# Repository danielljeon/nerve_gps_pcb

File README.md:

# nerve_gps_pcb

GPS module to [`nerve_pcb`](https://github.com/danielljeon/nerve_pcb).

---

<details markdown="1">
  <summary>Table of Contents</summary>

<!-- TOC -->
* [nerve_gps_pcb](#nerve_gps_pcb)
  * [1 Overview](#1-overview)
  * [2 Board Specifications](#2-board-specifications)
    * [2.1 Connectors](#21-connectors)
  * [3 Release Notes](#3-release-notes)
    * [3.1 v0.1.0-alpha](#31-v010-alpha)
    * [3.2 v0.1.0](#32-v010)
<!-- TOC -->

</details>

---

## 1 Overview

|                         Top                          |                           Bottom                           |                     v0.1.0-alpha                     |
|:----------------------------------------------------:|:----------------------------------------------------------:|:----------------------------------------------------:|
|  |  |  |

---

## 2 Board Specifications

### 2.1 Connectors

Connectors fixed by hardware (PCB traces or the connector itself).

| Connector                      | Ref | Description                                       |
|--------------------------------|:---:|---------------------------------------------------|
| Bottom side 2x8 board-to-board | J1  | See schematic/layout for details                  |
| WS2812B PWM breakout           | J2  | Pin 1: PWM RGB, Pin 2: Ground                     |
| 5 V GPIO breakout              | J3  | Pin 1: 5 V, Pin 2-4: GPIO1-3 (5 V), Pin 5: Ground |

---

## 3 Release Notes

### 3.1 v0.1.0-alpha

- Pre-release 4-layer board variant.
    - Short-term pre-release board bring-up/testing release.
- Order date: 2025/01/13.

### 3.2 v0.1.0

- Minor changes from the previous `v0.1.0-alpha` pre-release version.
    - Fixed the Double-inverted UART connection issue.

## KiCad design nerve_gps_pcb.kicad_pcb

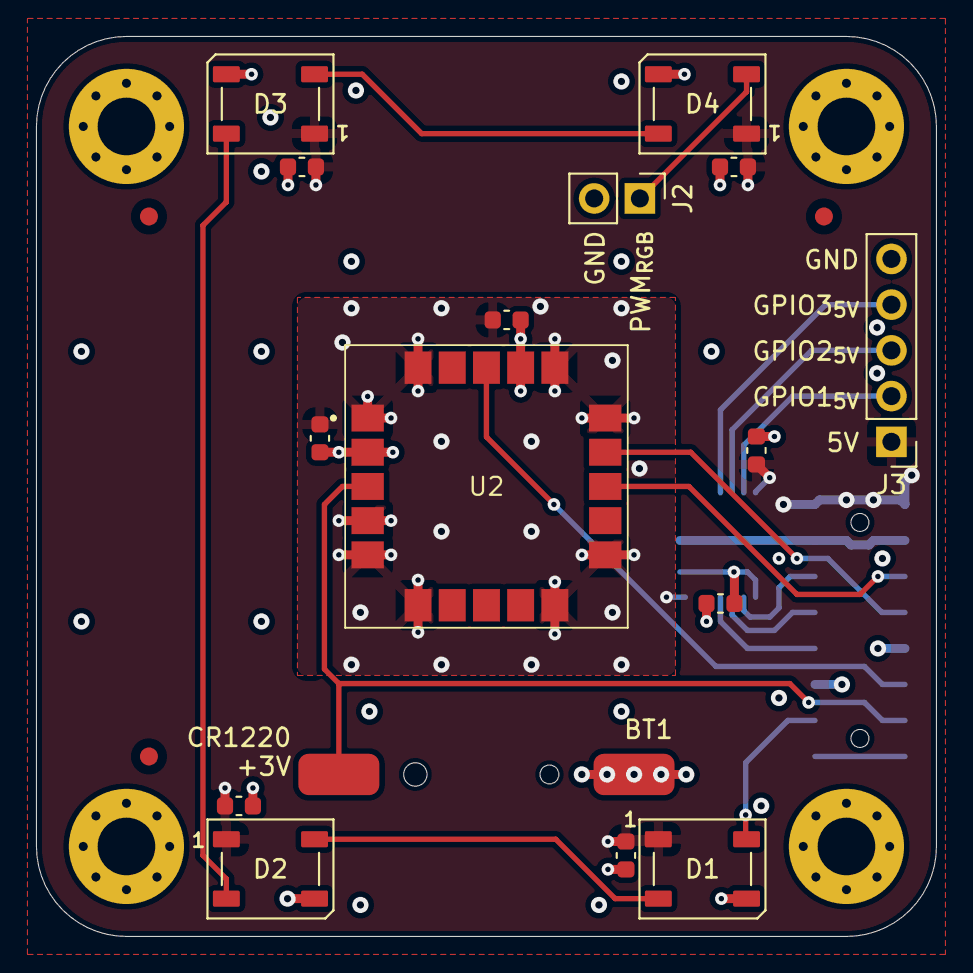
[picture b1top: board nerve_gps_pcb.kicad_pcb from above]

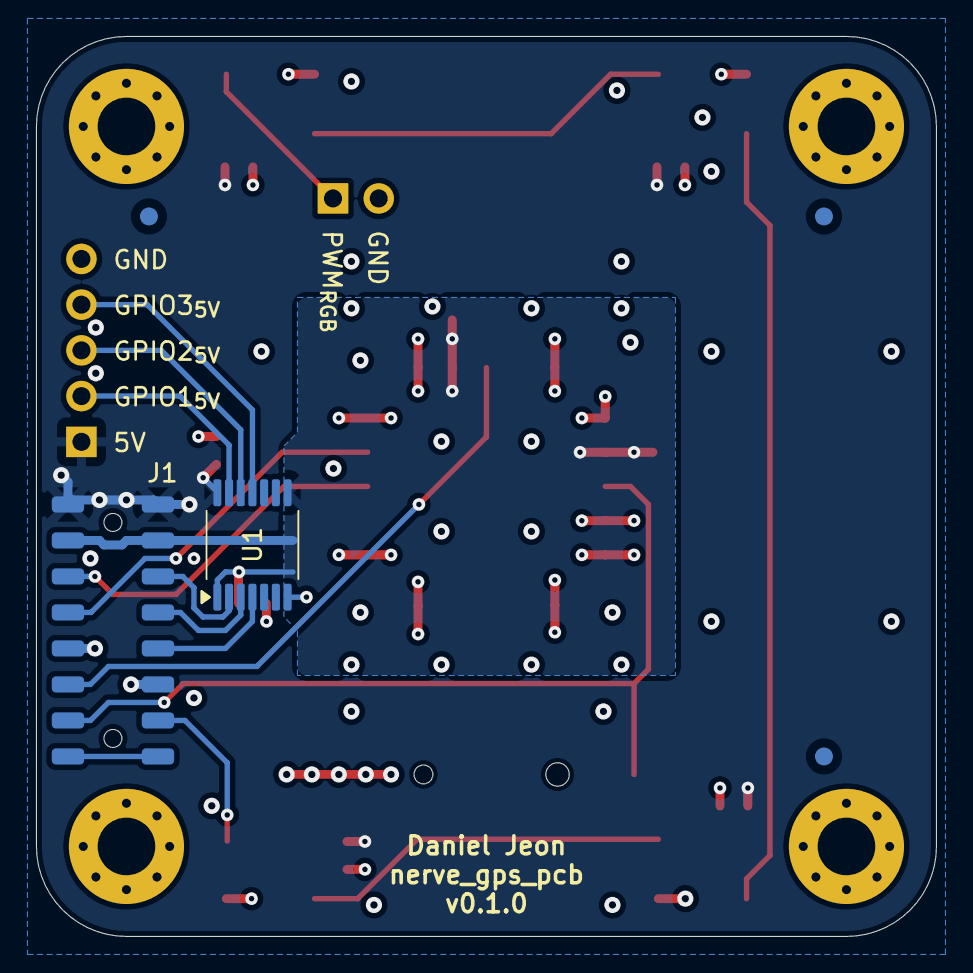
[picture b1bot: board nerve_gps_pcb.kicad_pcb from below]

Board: 4 copper layers, 50.0 x 50.0 mm, 28 parts (5 on the bottom side), 19 nets.

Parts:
BT1: CR1220; harwin_s8411-45r_cr1220_battery
C1, C2, C3, C4, C5, C6, C7, C8: 100n; C_0603_1608Metric
D1, D2, D3, D4: WS2812B; LED_WS2812B_PLCC4_5.0x5.0mm_P3.2mm
FM1, FM2, FM3, FM4, FM5, FM6: 1mm; Fiducial_1mm_Mask2mm
H1, H2, H3, H4: M3; MountingHole_3.2mm_M3_Pad_Via
J1: BF080-16-A-1-L-C; bf080-16-a-1-l-c
J2: WS2812B; PinHeader_1x02_P2.54mm_Vertical
J3: 5V GPIO Breakout; PinHeader_1x05_P2.54mm_Vertical
U1: TXB0104QPWRQ1; txb0104qpwrq1
U2: SAM-M10Q; ublox_sam

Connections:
+3V3: C1.1, C2.1, C3.1, J1.3, J1.4, U1.1 (V_{CCA}), U1.8 (OE), U2.2 (V_IO), U2.17 (VCC)
+3VBATT: BT1.2, J1.14, U2.3 (V_BCKP)
+5V: C4.1, C5.1, C6.1, C7.1, C8.1, D1.1 (VDD), D2.1 (VDD), D3.1 (VDD), D4.1 (VDD), J1.1, J1.2, J3.1, U1.14 (V_{CCB})
/GPIO_1: J1.5, U1.2 (A1)
/GPIO_1_{5V}: J3.2, U1.13 (B1)
/GPIO_2: J1.7, U1.3 (A2)
/GPIO_2_{5V}: J3.3, U1.12 (B2)
/GPIO_3: J1.9, U1.4 (A3)
/GPIO_3_{5V}: J3.4, U1.11 (B3)
/GPS_NRST: J1.12, U2.18 (RESET_N)
/GPS_UART_RX: J1.8, U2.14 (RXD)
/GPS_UART_TX: J1.6, U2.13 (TXD)
/LED_PWM_{5V}: D1.4 (DIN), J1.13
GND: BT1.1, C1.2, C2.2, C3.2, C4.2, C5.2, C6.2, C7.2, C8.2, D1.3 (VSS), D2.3 (VSS), D3.3 (VSS), D4.3 (VSS), H1.1, H2.1, H3.1, H4.1, J1.10, J1.11, J2.2, J3.5, U1.7 (GND), U2.1 (GND), U2.4 (GND), U2.5 (GND), U2.6 (GND), U2.10 (GND), U2.11 (GND), U2.15 (GND), U2.16 (GND), U2.20 (GND)
unnamed: D1.2 (DOUT), D2.4 (DIN)
unnamed: D2.2 (DOUT), D3.4 (DIN)
unnamed: D3.2 (DOUT), D4.4 (DIN)
unnamed: D4.2 (DOUT), J2.1
unnamed: J1.15, J1.16

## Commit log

2024-11-17 Add git and GitHub related files
2024-11-17 Add component_library submodule
2024-11-17 Fix attempt for broken submodule
2024-11-17 Add KiBot workflow
2024-11-17 Add WIP KiCad files
2024-11-17 Fix board-to-board connector pinout
2024-11-17 Move PCB dimensions to User Comments layer
2024-11-17 Pass DRC (ERC previously passed)
2024-11-18 Add KiBot badge in README.md
2024-11-19 Combine KiBot BoM directory
2024-11-19 Add stackup PCB notes
2024-11-19 Update KiBot PCB PDF gen
2024-11-20 Add ground stitching vias and silkscreen cleanup
2024-11-20 Fix bad vias
2024-11-22 Update component_library
2024-12-03 Add initial README.md and PCB pictures
2024-12-03 Update KiBot workflow
2024-12-08 Update docs pictures
2024-12-13 Cleanup and update board-to-board connector
2024-12-13 Add missing connectors library record
2024-12-13 Regenerate PCB
2025-01-03 Update config.kibot.yaml, cleanup, add fiducials
2025-01-09 Major cleanup and update component_library
2025-01-13 Cleanup silkscreen
2025-01-14 Update docs for release
2025-01-14 Fix README about v0.1.0-alpha
2025-01-14 Add MIT LICENSE file
2025-02-24 Fix #2
2025-02-24 Update versioning and docs pictures
2025-04-03 Update for KiCad 9.0 and component library
2025-04-03 Fix zone settings and cleanup silkscreen
2025-04-03 Update KiBot workflow to v2_k9
2025-04-03 Fix KiBot workflow for v2_k9
2025-04-03 Attempt fix KiBot footprint mismatch warning
2025-04-03 Attempt fix 2 KiBot footprint mismatch warning
2025-04-03 Update footprint and symbol library
2025-04-24 Standardize README.md
2025-05-05 Add minor decoupling caps
2025-05-14 Update README.md for PCB module reference
2025-05-16 Add CR1220 reverse polarity schottky diode
2025-05-27 Cleanup and fix outer layer non-functional pads
2025-06-03 Remove CR1220 schottky diode
2025-06-03 Update config.kibot.yaml for KiCad/Bot 9
2025-10-18 Add board picture
